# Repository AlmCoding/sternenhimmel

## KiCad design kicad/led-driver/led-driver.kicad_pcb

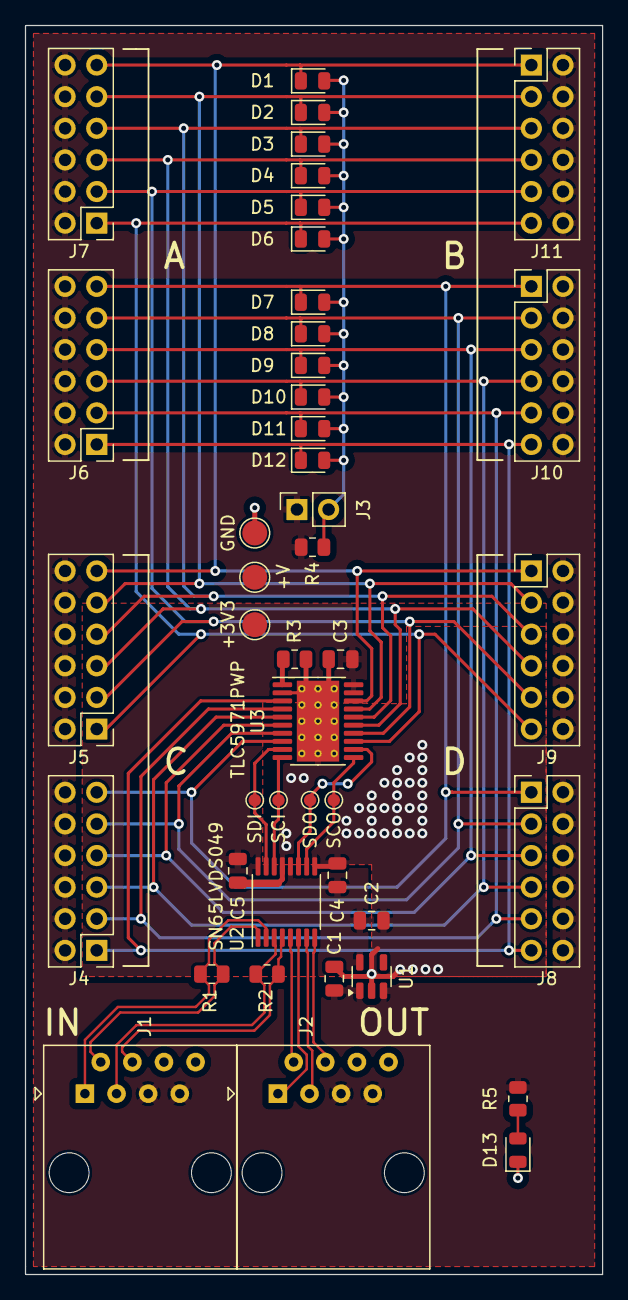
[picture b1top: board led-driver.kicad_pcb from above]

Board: 2 copper layers, 46.4 x 100.3 mm, 44 parts (0 on the bottom side), 30 nets.

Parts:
+3V3: TestPoint_Pad_D2.0mm
+V: TestPoint_Pad_D2.0mm
C1: 1uF; C_0805_2012Metric
C2: 10uF; C_0805_2012Metric
C3, C4: 100nF; C_0805_2012Metric
C5: 4nF; C_0805_2012Metric
D1, D2, D3, D4, D5, D6, D7, D8, D9, D10, D11, D12, D13: LED; LED_0805_2012Metric
GND: TestPoint_Pad_D2.0mm
J1, J2: RJ45; RJ45_Amphenol_54602-x08_Horizontal
J3: Conn_01x02_Pin; PinSocket_1x02_P2.54mm_Vertical
J4, J5, J6, J7, J8, J9, J10, J11: Conn_02x06_Odd_Even; PinHeader_2x06_P2.54mm_Vertical
R1, R2: 100; R_0805_2012Metric
R3: 2k4; R_0805_2012Metric
R4: 0; R_0805_2012Metric
R5: 2k; R_0805_2012Metric
SCI: TestPoint_Pad_D1.0mm
SCO: TestPoint_Pad_D1.0mm
SDI: TestPoint_Pad_D1.0mm
SDO: TestPoint_Pad_D1.0mm
U1: LP2985-33DBVR; SOT-23-5
U2: SN65LVDS049; TSSOP-16_4.4x5mm_P0.65mm
U3: TLC5971PWP; HTSSOP-20-1EP_4.4x6.5mm_P0.65mm_EP3.4x6.5mm_Mask2.75x3.43mm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

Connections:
+3V3: +3V3.1, C2.1, C3.1, C4.1, C5.1, U1.5 (VOUT), U2.12 (VCC), U2.16 (EN), U3.19 (VCC), U3.20 (VREG)
+12V: +V.1, C1.1, J1.5, J1.7, J2.5, J2.7, J3.1, J4.2, J4.4, J4.6, J4.8, J4.10, J4.12, J5.2, J5.4, J5.6, J5.8, J5.10, J5.12, J6.2, J6.4, J6.6, J6.8, J6.10, J6.12, J7.2, J7.4, J7.6, J7.8, J7.10, J7.12, J8.2, J8.4, J8.6, J8.8, J8.10, J8.12, J9.2, J9.4, J9.6, J9.8, J9.10, J9.12, J10.2, J10.4, J10.6, J10.8, J10.10, J10.12, J11.2, J11.4, J11.6, J11.8, J11.10, J11.12, R4.2, R5.1, U1.1 (VIN), U1.3 (EN)
/Cin_N: J1.3, R2.2, U2.3 (RIN2-)
/Cin_P: J1.4, R2.1, U2.4 (RIN2+)
/Cout_N: J2.3, U2.7 (DOUT1-)
/Cout_P: J2.4, U2.8 (DOUT1+)
/Din_N: J1.2, R1.2, U2.1 (RIN1-)
/Din_P: J1.1, R1.1, U2.2 (RIN1+)
/Dout_N: J2.2, U2.5 (DOUT2-)
/Dout_P: J2.1, U2.6 (DOUT2+)
GND: C1.2, C2.2, C3.2, C4.2, C5.2, D13.1 (K), GND.1, J1.6, J1.8, J2.6, J2.8, R3.2, U1.2 (GND), U2.9 (~EN), U2.13 (GND), U3.2 (GND), U3.21 (GND)
unnamed: D1.2 (A), D2.2 (A), D3.2 (A), D4.2 (A), D5.2 (A), D6.2 (A), D7.2 (A), D8.2 (A), D9.2 (A), D10.2 (A), D11.2 (A), D12.2 (A), J3.2, R4.1
unnamed: D1.1 (K), J5.11, J7.11, J9.1, J11.1, U3.18 (OUTB3)
unnamed: D2.1 (K), J5.9, J7.9, J9.3, J11.3, U3.17 (OUTG3)
unnamed: D3.1 (K), J5.7, J7.7, J9.5, J11.5, U3.16 (OUTR3)
unnamed: D4.1 (K), J5.5, J7.5, J9.7, J11.7, U3.15 (OUTB2)
unnamed: D5.1 (K), J5.3, J7.3, J9.9, J11.9, U3.14 (OUTG2)
unnamed: D6.1 (K), J5.1, J7.1, J9.11, J11.11, U3.13 (OUTR2)
unnamed: D7.1 (K), J4.11, J6.11, J8.1, J10.1, U3.8 (OUTB1)
unnamed: D8.1 (K), J4.9, J6.9, J8.3, J10.3, U3.7 (OUTG1)
unnamed: D9.1 (K), J4.7, J6.7, J8.5, J10.5, U3.6 (OUTR1)
unnamed: D10.1 (K), J4.5, J6.5, J8.7, J10.7, U3.5 (OUTB0)
unnamed: D11.1 (K), J4.3, J6.3, J8.9, J10.9, U3.4 (OUTG0)
unnamed: D12.1 (K), J4.1, J6.1, J8.11, J10.11, U3.3 (OUTR0)
unnamed: D13.2 (A), R5.2
unnamed: SCO.1, U2.10 (DIN1), U3.11 (SCKO)
unnamed: SDO.1, U2.11 (DIN2), U3.12 (SDTO)
unnamed: SDI.1, U2.15 (ROUT1), U3.9 (SDTI)
unnamed: SCI.1, U2.14 (ROUT2), U3.10 (SCKI)
unnamed: R3.1, U3.1 (IREF)

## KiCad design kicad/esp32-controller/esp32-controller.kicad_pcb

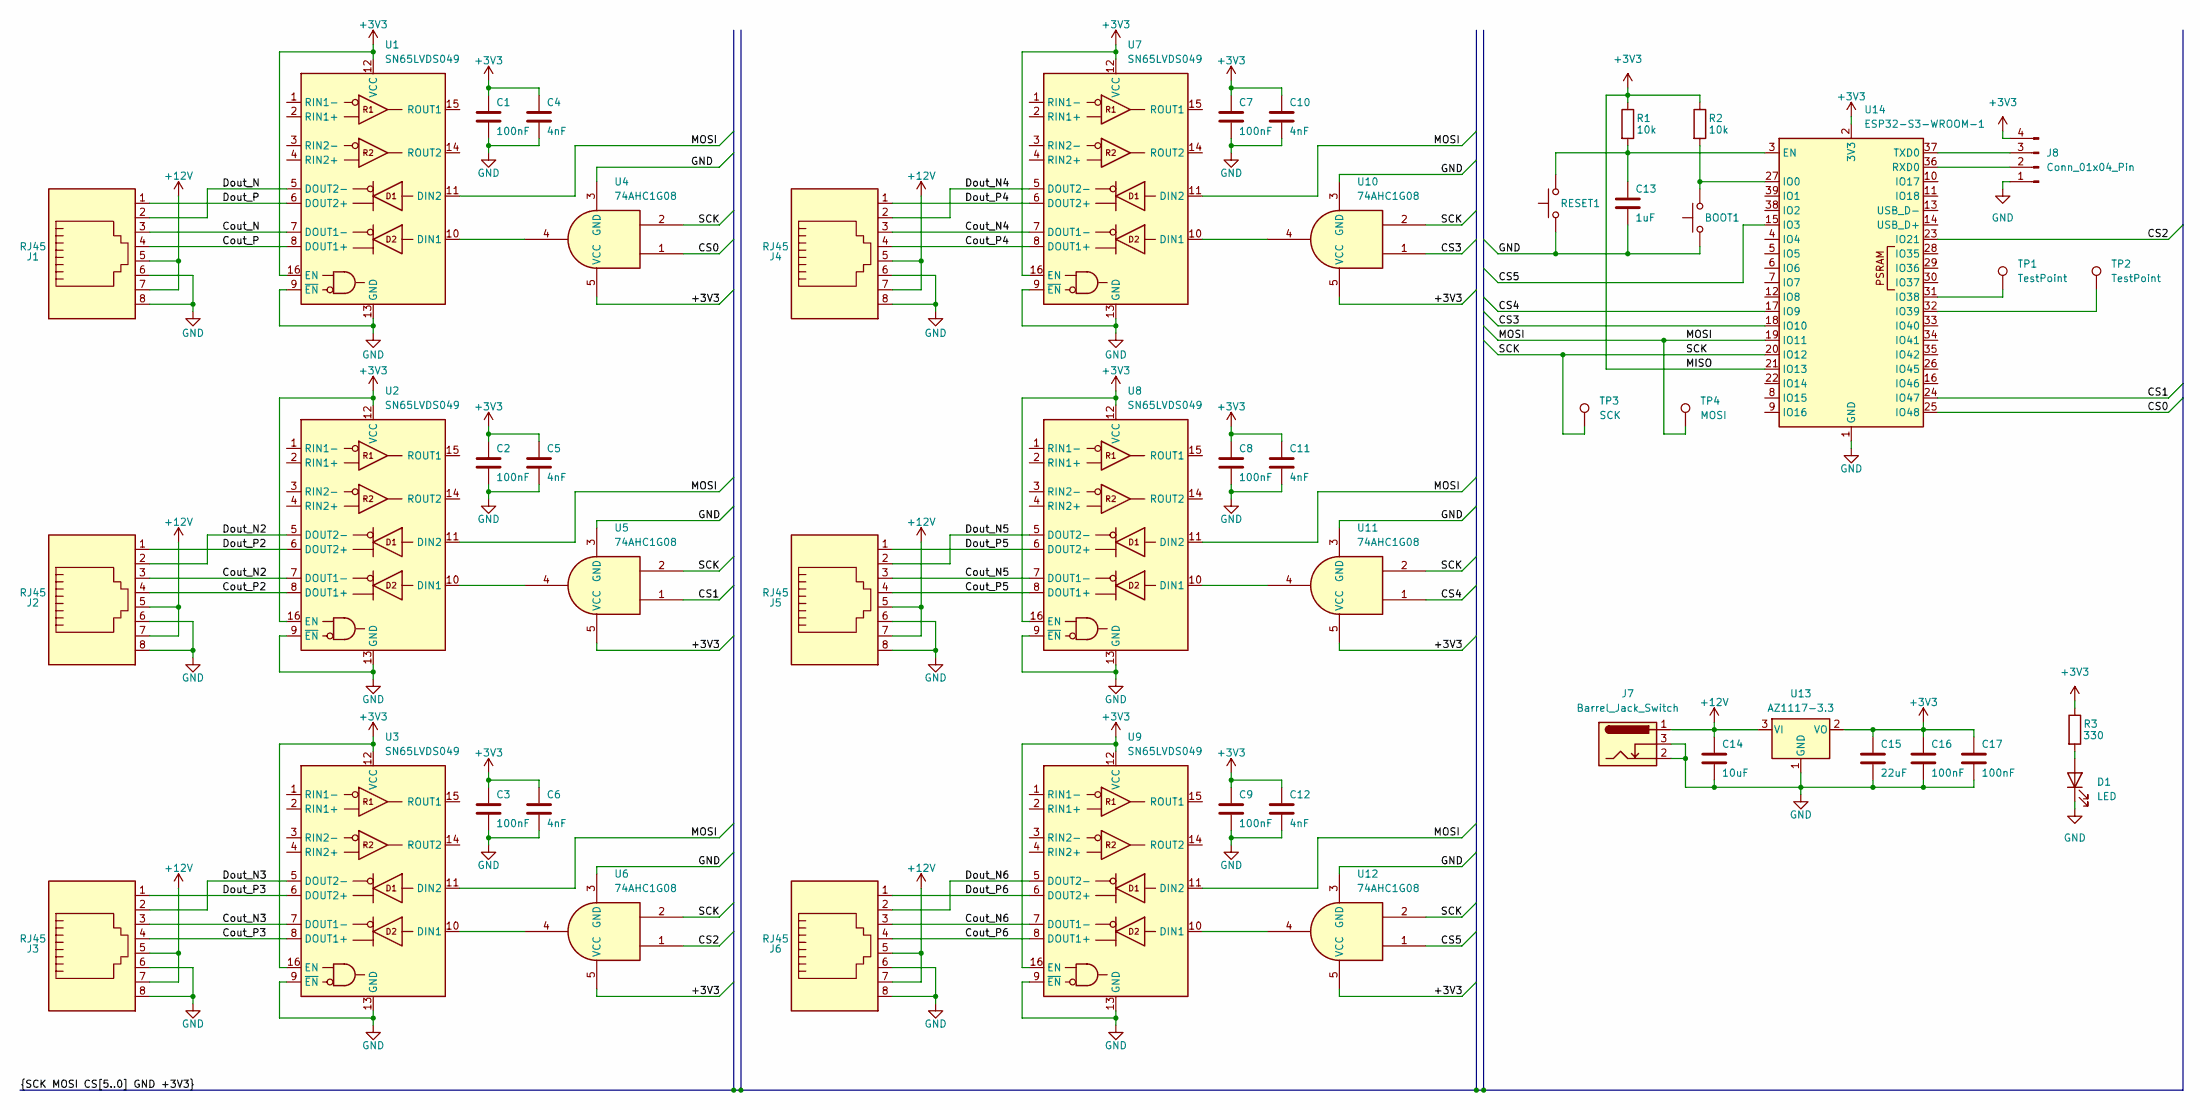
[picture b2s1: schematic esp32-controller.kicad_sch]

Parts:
BOOT1: SW_Omron_B3FS; SW_SPST_Omron_B3FS-100xP
C1, C2, C3, C7, C8, C9, C16, C17: 100nF; C_0805_2012Metric
C4, C5, C6, C10, C11, C12: 4nF; C_0805_2012Metric
C13: 1uF; C_0805_2012Metric
C14: 10uF; C_0805_2012Metric
C15: 22uF; C_0805_2012Metric
D1: LED; LED_0805_2012Metric
J1, J2, J3, J4, J5, J6: RJ45; RJ45_Amphenol_54602-x08_Horizontal
J7: Barrel_Jack_Switch; BarrelJack_Kycon_KLDX-0202-xC_Horizontal
J8: Conn_01x04_Pin; PinHeader_1x04_P2.54mm_Vertical
R1, R2: 10k; R_0805_2012Metric
R3: 330; R_0805_2012Metric
RESET1: SW_Omron_B3FS; SW_SPST_Omron_B3FS-100xP
TP1, TP2: TestPoint; TestPoint_Pad_D2.0mm
TP3: SCK; TestPoint_Pad_D1.5mm
TP4: MOSI; TestPoint_Pad_D1.5mm
U1, U2, U3, U7, U8, U9: SN65LVDS049; TSSOP-16_4.4x5mm_P0.65mm
U4, U5, U6, U10, U11, U12: 74AHC1G08; SOT-23-5_HandSoldering
U13: AZ1117-3.3; SOT-223-3_TabPin2
U14: ESP32-S3-WROOM-1

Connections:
+3V3: C1.1, C2.1, C3.1, C4.1, C5.1, C6.1, C7.1, C8.1, C9.1, C10.1, C11.1, C12.1, C15.1, C16.1, C17.1, J8.4, R1.1, R2.1, R3.1, U1.12 (VCC), U1.16 (EN), U2.12 (VCC), U2.16 (EN), U3.12 (VCC), U3.16 (EN), U4.5 (VCC), U5.5 (VCC), U6.5 (VCC), U7.12 (VCC), U7.16 (EN), U8.12 (VCC), U8.16 (EN), U9.12 (VCC), U9.16 (EN), U10.5 (VCC), U11.5 (VCC), U12.5 (VCC), U13.2 (VO), U14.2 (3V3), U14.21 (IO13); also elsewhere on the board
+12V: C14.1, J1.5, J1.7, J2.5, J2.7, J3.5, J3.7, J4.5, J4.7, J5.5, J5.7, J6.5, J6.7, J7.1, U13.3 (VI); also elsewhere on the board
/CS0: U4.1, U14.25 (IO48)
/CS1: U5.1, U14.24 (IO47)
/CS2: U6.1, U14.23 (IO21)
/CS3: U10.1, U14.18 (IO10)
/CS4: U11.1, U14.17 (IO9)
/CS5: U12.1, U14.15 (IO3)
/Cout_N: J1.3, U1.7 (DOUT1-)
/Cout_N2: J2.3, U2.7 (DOUT1-)
/Cout_N3: J3.3, U3.7 (DOUT1-)
/Cout_N4: J4.3, U7.7 (DOUT1-)
/Cout_N5: J5.3, U8.7 (DOUT1-)
/Cout_N6: J6.3, U9.7 (DOUT1-)
/Cout_P: J1.4, U1.8 (DOUT1+)
/Cout_P2: J2.4, U2.8 (DOUT1+)
/Cout_P3: J3.4, U3.8 (DOUT1+)
/Cout_P4: J4.4, U7.8 (DOUT1+)
/Cout_P5: J5.4, U8.8 (DOUT1+)
/Cout_P6: J6.4, U9.8 (DOUT1+)
/Dout_N: J1.2, U1.5 (DOUT2-)
/Dout_N2: J2.2, U2.5 (DOUT2-)
/Dout_N3: J3.2, U3.5 (DOUT2-)
/Dout_N4: J4.2, U7.5 (DOUT2-)
/Dout_N5: J5.2, U8.5 (DOUT2-)
/Dout_N6: J6.2, U9.5 (DOUT2-)
/Dout_P: J1.1, U1.6 (DOUT2+)
/Dout_P2: J2.1, U2.6 (DOUT2+)
/Dout_P3: J3.1, U3.6 (DOUT2+)
/Dout_P4: J4.1, U7.6 (DOUT2+)
/Dout_P5: J5.1, U8.6 (DOUT2+)
/Dout_P6: J6.1, U9.6 (DOUT2+)
/MOSI: TP4.1, U1.11 (DIN2), U2.11 (DIN2), U3.11 (DIN2), U7.11 (DIN2), U8.11 (DIN2), U9.11 (DIN2), U14.19 (IO11)
/SCK: TP3.1, U4.2, U5.2, U6.2, U10.2, U11.2, U12.2, U14.20 (IO12)
GND: BOOT1.1, C1.2, C2.2, C3.2, C4.2, C5.2, C6.2, C7.2, C8.2, C9.2, C10.2, C11.2, C12.2, C13.2, C14.2, C15.2, C16.2, C17.2, D1.1 (K), J1.6, J1.8, J2.6, J2.8, J3.6, J3.8, J4.6, J4.8, J5.6, J5.8, J6.6, J6.8, J7.2, J7.3, J8.1, RESET1.1, U1.9 (~EN), U1.13 (GND), U2.9 (~EN), U2.13 (GND), U3.9 (~EN), U3.13 (GND), U4.3 (GND), U5.3 (GND), U6.3 (GND), U7.9 (~EN), U7.13 (GND), U8.9 (~EN), U8.13 (GND), U9.9 (~EN), U9.13 (GND), U10.3 (GND), U11.3 (GND), U12.3 (GND), U13.1 (GND), U14.1 (GND), U14.40 (GND), U14.41 (GND); also elsewhere on the board
unnamed: D1.2 (A), R3.2
unnamed: J8.2, U14.36 (RXD0)
unnamed: J8.3, U14.37 (TXD0)
unnamed: U1.10 (DIN1), U4.4
unnamed: U2.10 (DIN1), U5.4
unnamed: U3.10 (DIN1), U6.4
unnamed: U7.10 (DIN1), U10.4
unnamed: U8.10 (DIN1), U11.4
unnamed: U9.10 (DIN1), U12.4
unnamed: C13.1, R1.2, RESET1.2, U14.3 (EN)
unnamed: BOOT1.2, R2.2, U14.27 (IO0)
unnamed: TP1.1, U14.31 (IO38)
unnamed: TP2.1, U14.32 (IO39)

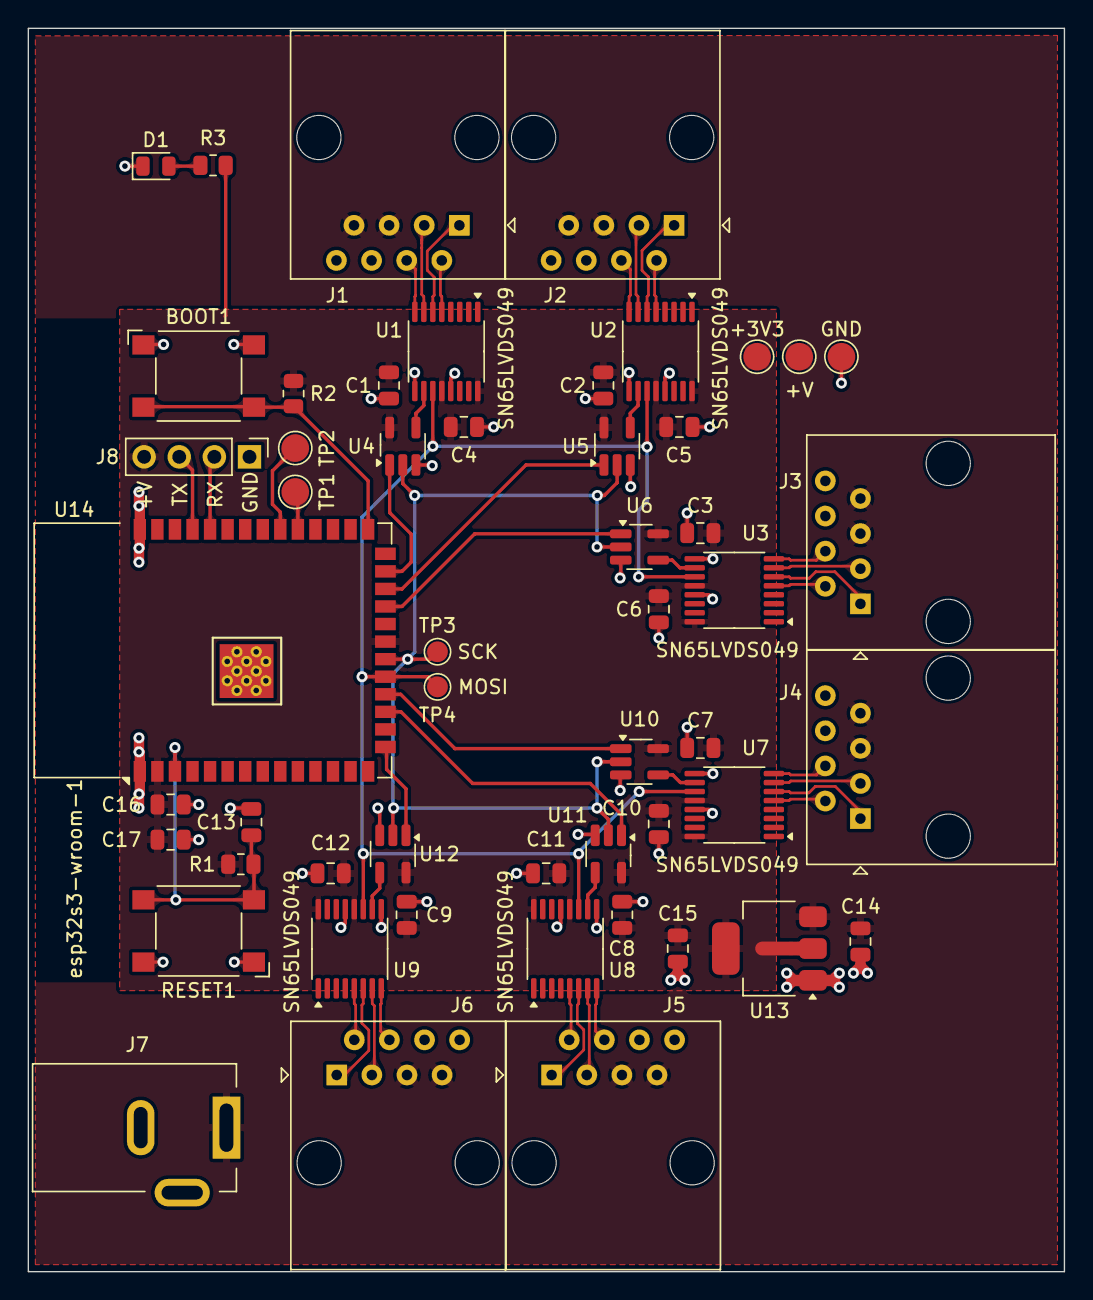
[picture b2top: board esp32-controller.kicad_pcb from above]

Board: 2 copper layers, 74.9 x 89.9 mm, 52 parts (0 on the bottom side), 48 nets.

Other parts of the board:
+3V3: TestPoint_Pad_D2.0mm
+V: TestPoint_Pad_D2.0mm
GND: TestPoint_Pad_D2.0mm

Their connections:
+3V3: +3V3.1; also elsewhere on the board
+12V: +V.1; also elsewhere on the board
GND: GND.1; also elsewhere on the board

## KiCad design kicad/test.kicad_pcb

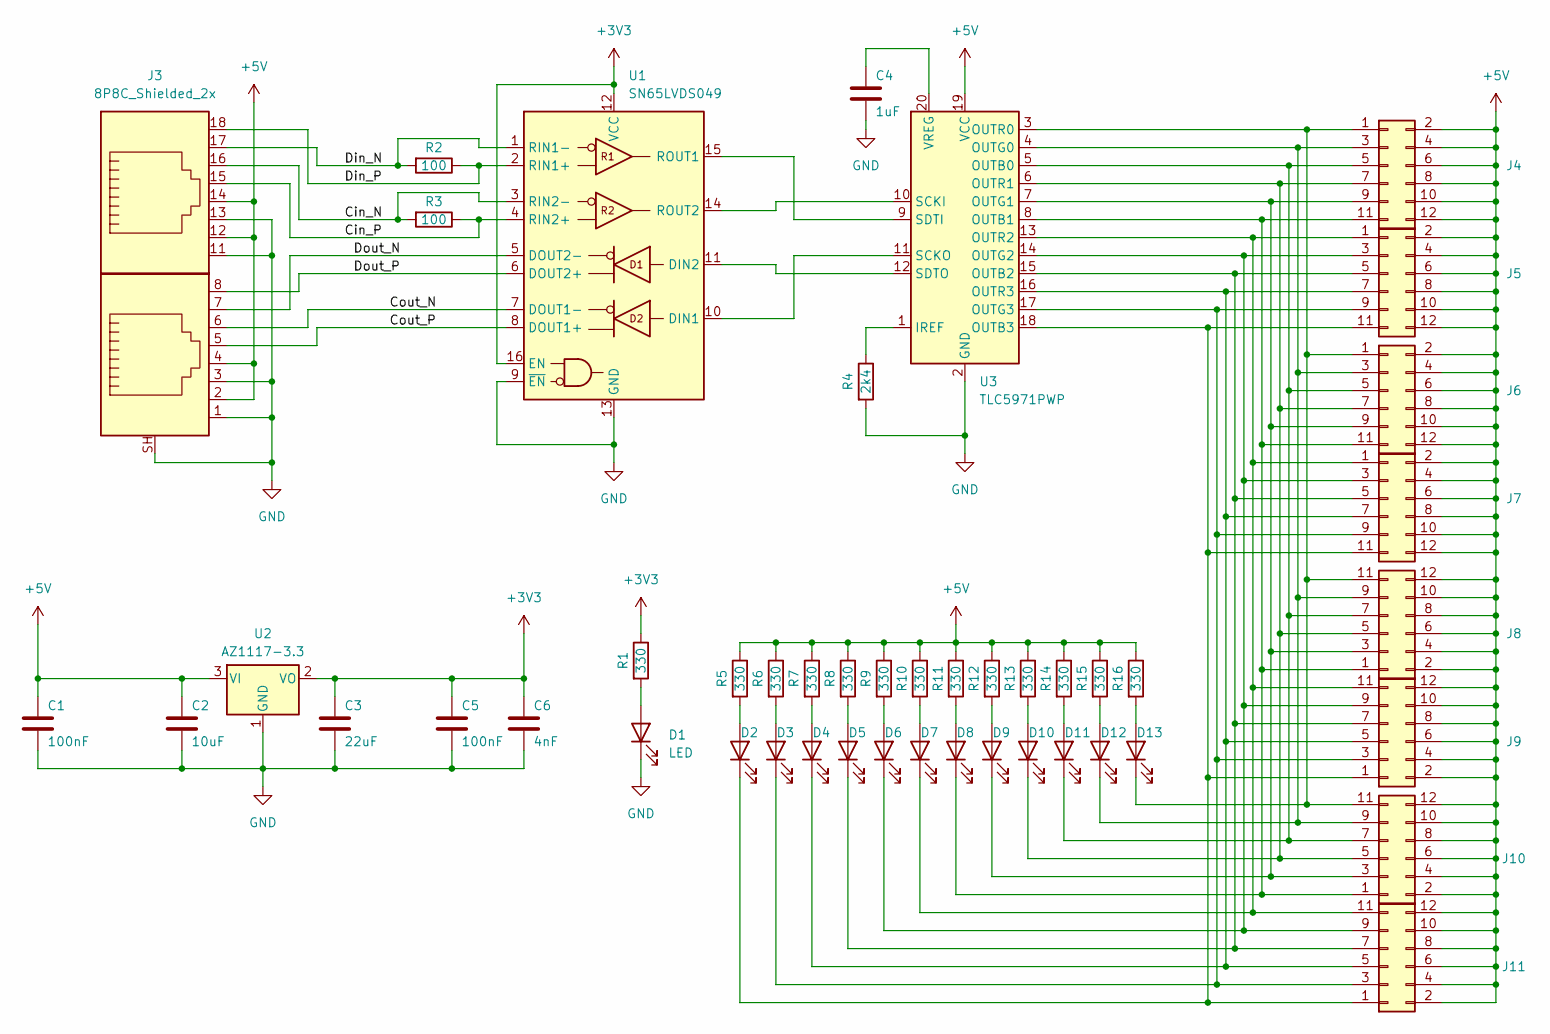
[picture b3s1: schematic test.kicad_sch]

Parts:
C1, C5: 100nF; C_0805_2012Metric
C2: 10uF; C_0805_2012Metric
C3: 22uF; C_0805_2012Metric
C4: 1uF; C_0805_2012Metric
C6: 4nF; C_0805_2012Metric
D1, D2, D3, D4, D5, D6, D7, D8, D9, D10, D11, D12, D13: LED; LED_0805_2012Metric
J3: 8P8C_Shielded_2x; RJ45_2x
J4, J5, J6, J7, J8, J9, J10, J11: Conn_02x06_Odd_Even; PinHeader_2x06_P2.54mm_Vertical
R1, R5, R6, R7, R8, R9, R10, R11, R12, R13, R14, R15, R16: 330; R_0805_2012Metric
R2, R3: 100; R_0805_2012Metric
R4: 2k4; R_0805_2012Metric
U1: SN65LVDS049; TSSOP-16_4.4x5mm_P0.65mm
U2: AZ1117-3.3; SOT-223-3_TabPin2
U3: TLC5971PWP; HTSSOP-20-1EP_4.4x6.5mm_P0.65mm_EP3.4x6.5mm_Mask2.75x3.43mm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

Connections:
+3V3: C3.1, C5.1, C6.1, R1.1, U1.12 (VCC), U1.16 (EN), U2.2 (VO)
+5V: C1.1, C2.1, J3.2, J3.4, J3.12, J3.14, J4.2, J4.4, J4.6, J4.8, J4.10, J4.12, J5.2, J5.4, J5.6, J5.8, J5.10, J5.12, J6.2, J6.4, J6.6, J6.8, J6.10, J6.12, J7.2, J7.4, J7.6, J7.8, J7.10, J7.12, J8.2, J8.4, J8.6, J8.8, J8.10, J8.12, J9.2, J9.4, J9.6, J9.8, J9.10, J9.12, J10.2, J10.4, J10.6, J10.8, J10.10, J10.12, J11.2, J11.4, J11.6, J11.8, J11.10, J11.12, R5.1, R6.1, R7.1, R8.1, R9.1, R10.1, R11.1, R12.1, R13.1, R14.1, R15.1, R16.1, U2.3 (VI), U3.19 (VCC)
/Cin_N: J3.16, R3.2, U1.3 (RIN2-)
/Cin_P: J3.15, R3.1, U1.4 (RIN2+)
/Cout_N: J3.6, U1.7 (DOUT1-)
/Cout_P: J3.5, U1.8 (DOUT1+)
/Din_N: J3.17, R2.2, U1.1 (RIN1-)
/Din_P: J3.18, R2.1, U1.2 (RIN1+)
/Dout_N: J3.7, U1.5 (DOUT2-)
/Dout_P: J3.8, U1.6 (DOUT2+)
GND: C1.2, C2.2, C3.2, C4.2, C5.2, C6.2, D1.1 (K), J3.1, J3.3, J3.11, J3.13, J3.SH, R4.2, U1.9 (~EN), U1.13 (GND), U2.1 (GND), U3.2 (GND), U3.21 (GND)
unnamed: D1.2 (A), R1.2
unnamed: D2.2 (A), R5.2
unnamed: D2.1 (K), J5.11, J7.11, J9.1, J11.1, U3.18 (OUTB3)
unnamed: D3.2 (A), R6.2
unnamed: D3.1 (K), J5.9, J7.9, J9.3, J11.3, U3.17 (OUTG3)
unnamed: D4.2 (A), R7.2
unnamed: D4.1 (K), J5.7, J7.7, J9.5, J11.5, U3.16 (OUTR3)
unnamed: D5.2 (A), R8.2
unnamed: D5.1 (K), J5.5, J7.5, J9.7, J11.7, U3.15 (OUTB2)
unnamed: D6.2 (A), R9.2
unnamed: D6.1 (K), J5.3, J7.3, J9.9, J11.9, U3.14 (OUTG2)
unnamed: D7.2 (A), R10.2
unnamed: D7.1 (K), J5.1, J7.1, J9.11, J11.11, U3.13 (OUTR2)
unnamed: D8.2 (A), R11.2
unnamed: D8.1 (K), J4.11, J6.11, J8.1, J10.1, U3.8 (OUTB1)
unnamed: D9.2 (A), R12.2
unnamed: D9.1 (K), J4.9, J6.9, J8.3, J10.3, U3.7 (OUTG1)
unnamed: D10.2 (A), R13.2
unnamed: D10.1 (K), J4.7, J6.7, J8.5, J10.5, U3.6 (OUTR1)
unnamed: D11.2 (A), R14.2
unnamed: D11.1 (K), J4.5, J6.5, J8.7, J10.7, U3.5 (OUTB0)
unnamed: D12.2 (A), R15.2
unnamed: D12.1 (K), J4.3, J6.3, J8.9, J10.9, U3.4 (OUTG0)
unnamed: D13.2 (A), R16.2
unnamed: D13.1 (K), J4.1, J6.1, J8.11, J10.11, U3.3 (OUTR0)
unnamed 36: U1.10 (DIN1), U3.11 (SCKO); also elsewhere on the board
unnamed 37: U1.11 (DIN2), U3.12 (SDTO); also elsewhere on the board
unnamed 38: U1.15 (ROUT1), U3.9 (SDTI); also elsewhere on the board
unnamed 39: U1.14 (ROUT2), U3.10 (SCKI); also elsewhere on the board
unnamed: R4.1, U3.1 (IREF)
unnamed: C4.1, U3.20 (VREG)

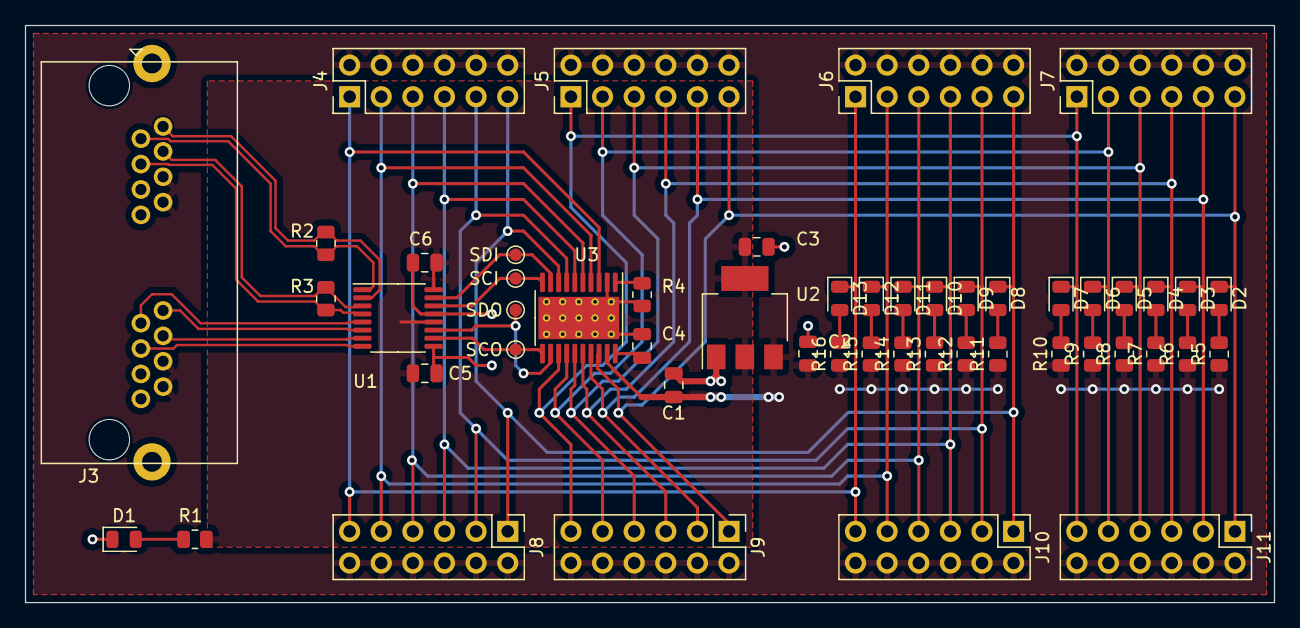
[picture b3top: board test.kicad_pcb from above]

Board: 2 copper layers, 100.3 x 46.4 mm, 51 parts (0 on the bottom side), 42 nets.

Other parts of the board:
SCI: TestPoint_Pad_D1.0mm
SCO: TestPoint_Pad_D1.0mm
SDI: TestPoint_Pad_D1.0mm
SDO: TestPoint_Pad_D1.0mm

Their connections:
unnamed 36: SCO.1; also elsewhere on the board
unnamed 37: SDO.1; also elsewhere on the board
unnamed 38: SDI.1; also elsewhere on the board
unnamed 39: SCI.1; also elsewhere on the board

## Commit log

2019-01-25 Init with last project state
2019-01-25 First version with 40 elements
2019-09-13 add ino
2019-09-13 add mcp23017 library
2019-09-14 add gpio expanders
2019-09-15 prog
2019-09-15 save
2019-09-15 add output transform
2019-09-29 update output trafo
2019-09-30 play show
2019-10-08 add playback
2019-10-09 finish playback
2019-10-12 fine tuning
2019-10-12 add offset, cleanup, finalize v1.0
2019-10-12 change passwd
2019-11-03 connector shift
2019-11-24 add layout
2019-11-24 clean up
2023-04-20 Refactor code
2023-04-21 Add seq parser
2023-04-22 Finish play sequence
2023-04-23 Fix step reps
2023-04-23 Add mcp simulation
2023-04-23 Reformat code
2023-04-23 Fix out2mcp pin
2023-04-23 Fix debug switch
2023-04-23 Release build
2023-04-23 Refactoring
2024-05-05 Add things
2024-12-30 Save progress
2024-12-30 Add esp32 expander
2024-12-31 port to esp32
2025-01-01 V1.0
2025-01-01 Cleanup
2025-01-02 Fix led driver vcc
2025-01-02 v2-production
2025-01-02 fix vreg on led driver
2025-01-13 Add sketch for daisy chain
2025-01-13 Add calibration values
2025-01-15 Implement Player
2025-01-16 Enable tear drops on PCB
2025-01-16 Add power test points
2025-01-23 Update PCBs
2025-01-24 Complete controller PCB v1
2025-01-24 Progress
2025-02-02 Improve thermal props
2025-02-03 Thermal refactoring
2025-02-06 Migrate to 3 chain setup
2025-02-08 Move to 3 chain setup
2025-03-05 Complete controller pcb
2025-07-18 Refactor controller pcb
2025-08-02 Fix pcb + software
2025-08-04 Write tlc class
2025-08-04 Add testpoints to pcbs
2025-08-19 Add default values + refactoring
2025-08-20 Add BLE setup
2025-08-23 Add data chunking
2025-08-25 Implement cmds
2025-08-26 Refactor config tool app
2025-08-26 Add GUI
2025-08-26 Add led changed filter on upload
2025-08-27 Add get info
2025-08-27 Build release V0.0.1
2025-08-27 Add play show to esp32 + fix python shallow copy bug
2025-08-28 Add send command feature
2025-08-28 Fix led enumeration
2025-08-28 ConfigToolApp Release V0.0.2
2025-08-28 Set idle values in config file
2025-08-29 Fix esp32 ble rx timeout bug
2025-08-29 DaisyChain Release V0.0.2
2025-08-29 Add chain statistics calculation
2025-08-30 ConfigToolApp Release V0.0.3
2025-08-30 Update led linearization gamma
2025-08-30 DaisyChain Release V0.0.3
    Add BLE OTA support
2025-08-31 Add BLE OTA to ConfigTool
2025-08-31 Add log message callback handling
2025-08-31 Speed up logging
2025-09-01 ConfigTool Release V0.0.4
    Add OTA feature
2025-09-01 Refactor class names
2025-09-01 DaisyChain V0.0.4 and ConfigTool V0.0.5 Release
2025-09-02 Release LEDpcb V0.1 and ESPpcb V0.1
2025-09-07 Run periodic chain refresh
2025-09-07 Add disable hardware option for BLE testing
2025-09-07 DaisyChain Release V0.0.5
    Add periodic chain refresh
